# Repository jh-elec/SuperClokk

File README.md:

# SuperClokk

/*
*   8 x 8 LED Matrix Uhr
* 
* - BMP180  ( Luftdruck / Temperatur )
* - RX8564  ( RTC - Echtzeituhr )
* - DCF77   ( Uhrzeit  Funkempfänger )
*/

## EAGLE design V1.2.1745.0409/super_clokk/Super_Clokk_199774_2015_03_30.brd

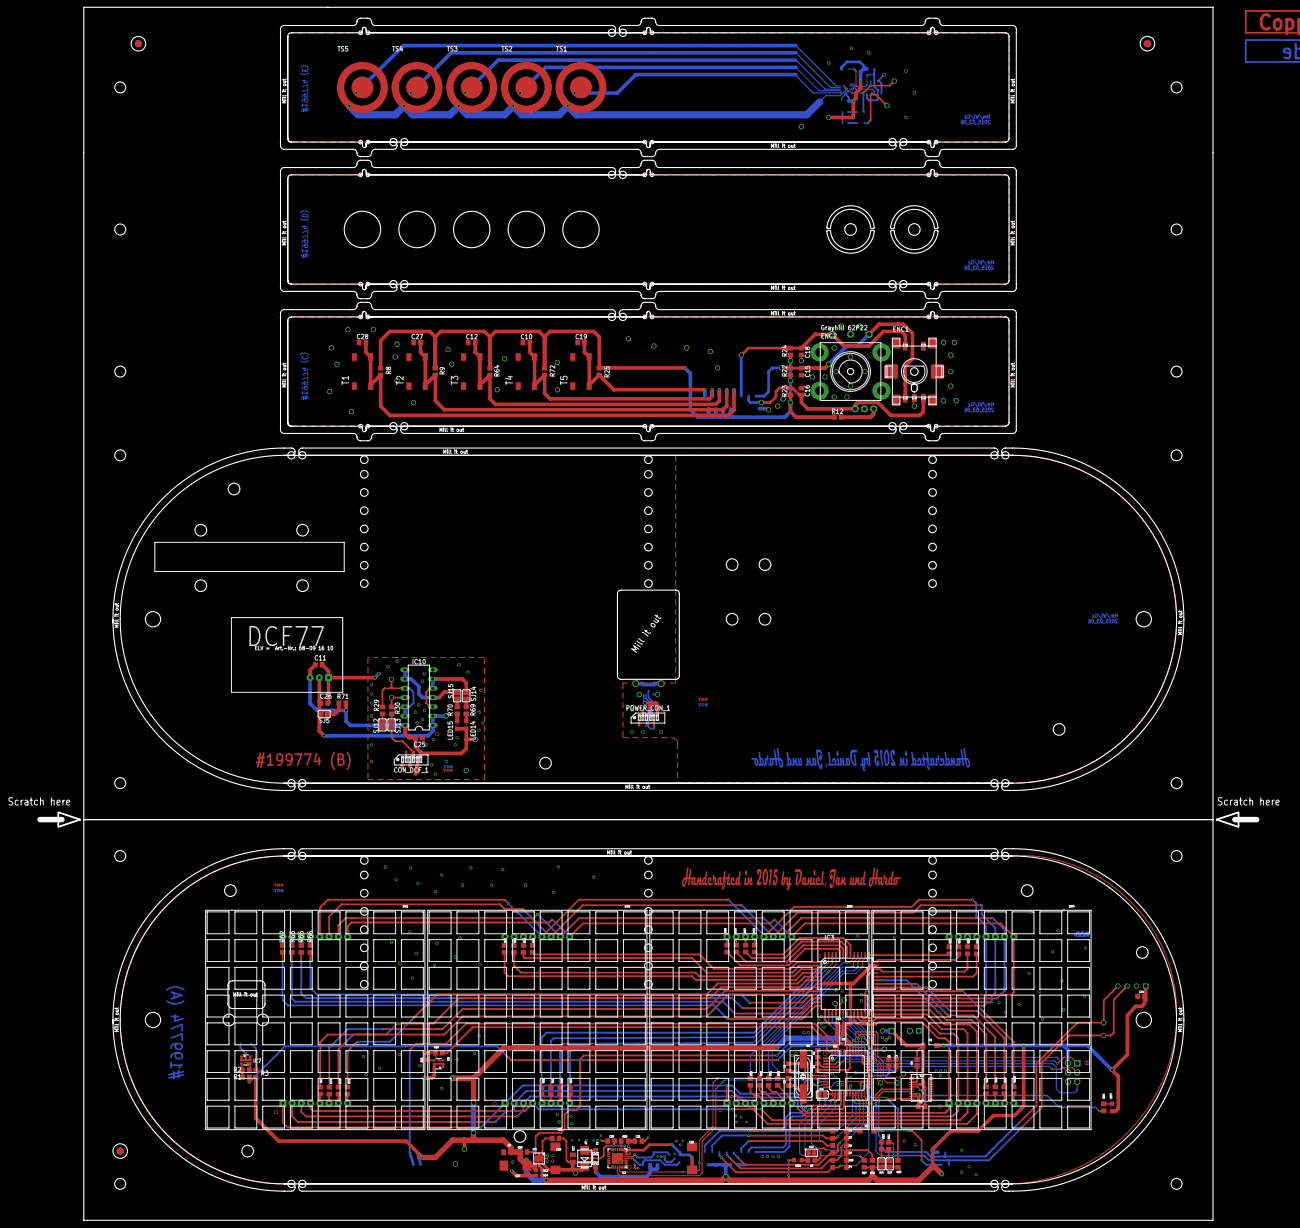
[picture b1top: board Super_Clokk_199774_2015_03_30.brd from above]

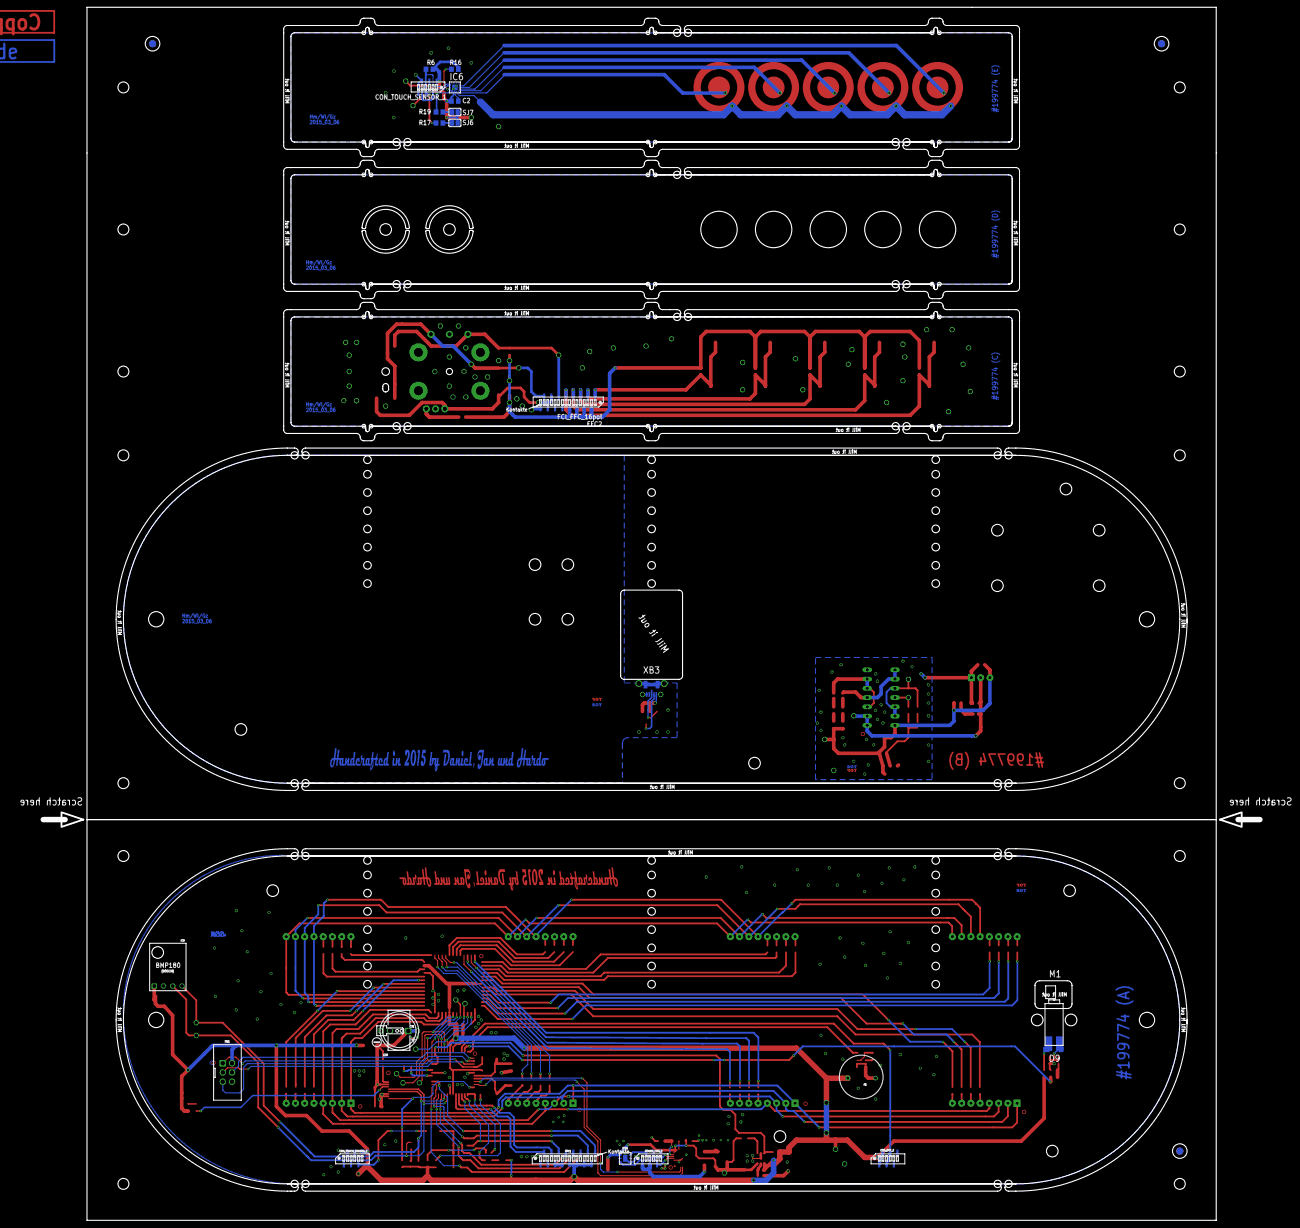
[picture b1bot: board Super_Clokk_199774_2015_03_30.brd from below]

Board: 2 copper layers, 334.0 x 333.0 mm, 211 parts (28 on the bottom side), 175 nets.

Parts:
A1: FUCW03THT; FUCW03
A3: ELV68-09-16-10; 18X23MM
C1, C2, C5, C6, C7, C9, C10, C11, C12, C14, C15, C16, C18, C19, C20, C21, C24, C25, C27, C28: 100n; C0805
C3, C4: 22p; C0805K
C8, C17: 1u; C0805K
C22, C23, C29: 100µ; SMC_D
C26: 10n; C0805
C30: PANASONIC_SD_SERIES_STEHEND
C31: PANASONIC_SD_SERIES_LIEGEND
CON_DCF_1, CON_DCF_2: MOLEX_52808_0671_NON_ZIF; MOLEX_52808-0671_NON_ZIF
CON_TOUCH_SENSOR_1, CON_TOUCH_SENSOR_2: MOLEX_52808_0671_NON_ZIF; MOLEX_52808-0671_NON_ZIF
D1, D2, D3, D4, D5, D6, D8, D9, D10: BAS116H-115; SOD123
D7: SS24R4; DO-214AA/SMB
DIS1, DIS2, DIS3, DIS4: TOYO-D24882; TOYO
ENC1: BOURNS_PEC11S
ENC2: Grayhill 62P22; 62P22
F2: MF-NSMF200; 1206L
FFC1, FFC2: FCI_FFC_16pol; MOLEX_52808_1671_NON_ZIF
IC1: CP2102SMD; QFN28
IC2: VSOJ20
IC3: HT1632-C; 52PIN_OFP
IC4: LD39050PUR; DFN6
IC5, IC7: PMN28-UN; SOT457
IC6: AT42QT2120-MMH; VQFN-20
IC8: MEGA32-A; TQFP44
IC9: BOSCH-BMP180; 10X13MM
IC10: 4093N; DIL14
IC11: TPD2E001DRSR; DRS
LED2, LED7, LED14, LED15: CHIPLED_0805
M1: VIBROMOTORTHT432A; LA4-432A
MAINFRAME: PLATINENKONTUR_310X220_FULLY_ROUNDED
POWER_CON_1, POWER_CON_2: FCI_FFC_6_pol; MOLEX_52808-0671_NON_ZIF
Q2: HC49-U / 16 MHz; HC49
R1, R4, R5, R10, R18, R29, R30, R69, R70: 1k; R0805
R2, R7, R8, R9, R11, R15, R20, R21, R25, R26, R27, R28, R64, R71, R72: 100k; R0805
R3: 47R; R0805
R6, R16, R17, R19, R22, R23, R24: 10k; R0805
R12: 100R; R0805
R13: 470k; R0603
R14: 150k; R0603
R52, R53: 4,7k; R0805
R62, R63, R65, R66, R67, R74, R75, R76, R77, R78, R79, R80, R81, R82, R83, R84, R85, R86, R87, R88, R89, R90, R91, R92, R93, R94, R95, R96, R97, R98, R99, R100: 22R; R0805
REF1, REF2, REF3: PASSER_2MM
SJ1, SJ2, SJ3, SJ4, SJ5, SJ6, SJ7, SJ12, SJ13, SJ14, SJ15: SJ
T1, T2, T3, T4, T5: OMRON-B3S-1002P; B3S-1002P
TP1, TP2, TP3, TP4, TP5, TP6, TP7, TP8, TP9, TP10, TP11, TP12, TP13, TP14, TP15, TP16, TP17, TP18, TP19, TP20: THT-1X2,54
TS1, TS2, TS3, TS4, TS5: TOUCH_SENSOR_14MM
U$1, U$6, U$8: BOT
U$2, U$9: HANDCRAFTED_WL_HM_GZ
U$3, U$4, U$5: TOP
U$7, U$24: WENN_GIRLSDAY_DANN_NUR_BEI_HESCH_LAYER_2
U$10, U$11, U$13: BESCHRIFTUNG_MECHANISCHE_TASTEN
U$12: WENN_GIRLSDAY_DANN_NUR_BEI_HESCH_LAYER_15
U$17, U$21, U$22, U$23: HESCH_LOGO_BIENE_LAYER_15
U$18, U$19, U$20: HESCH_LOGO_BIENE_LAYER_2
XB3: MICRODX4R005JJ2; MICRO_NEU
XW1: WSL

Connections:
+3V3: A1.+, C8.1, C9.1, C14.2, C23.+, C24.1, CON_DCF_2.1, CON_DCF_2.2, CON_TOUCH_SENSOR_2.6, D1.A, FFC1.9, FFC1.11, FFC1.13, FFC1.15, IC3.7, IC3.21, IC3.38, IC4.4, IC8.5, IC8.17, IC8.38, IC9.1, LED2.A, LED7.A, R3.1, R7.2, R13.1, R15.1, R20.2, R26.2, R27.2, SJ3.2, SJ4.2, TP8.TP, XW1.2
+3V3_TOUCH_SENSOR_MODUL: C2.1, CON_TOUCH_SENSOR_1.1, IC6.9, R6.2, R16.2, SJ6.2, SJ7.2, TP19.TP
ABORT_ALL_FUNCTIONS: C19.1, FFC2.1, R25.2, T5.1, T5.2
ABORT_ALL_FUNCTIONS_TO_CONNECTOR: D2.C, FFC1.16, IC8.25
AREF: C7.1, IC8.29
AVCC: C6.1, IC8.27
CHANGE_INT_TOUCH: CON_TOUCH_SENSOR_1.2, IC6.15, R6.1
CLKOUT: IC2.5, R18.1
COL_0: DIS1.1, DIS2.1, DIS3.1, DIS4.1, IC3.22
COL_1: DIS1.2, DIS2.2, DIS3.2, DIS4.2, IC3.23
COL_2: DIS1.3, DIS2.3, DIS3.3, DIS4.3, IC3.24
COL_3: DIS1.4, DIS2.4, DIS3.4, DIS4.4, IC3.26
COL_4: DIS1.12, DIS2.12, DIS3.12, DIS4.12, IC3.27
COL_5: DIS1.11, DIS2.11, DIS3.11, DIS4.11, IC3.28
COL_6: DIS1.10, DIS2.10, DIS3.10, DIS4.10, IC3.29
COL_7: DIS1.9, DIS2.9, DIS3.9, DIS4.9, IC3.30
CP2102_RESET: IC1.9, R28.2
CP2102_RXD: IC1.25, IC8.10
CP2102_TXD: IC1.26, IC8.9
D1_ROW0: DIS1.16, R62.1
D1_ROW1: DIS1.15, R63.1
D1_ROW2: DIS1.14, R65.1
D1_ROW3: DIS1.13, R66.1
D1_ROW4: DIS1.5, R67.1
D1_ROW5: DIS1.6, R74.1
D1_ROW6: DIS1.7, R75.1
D1_ROW7: DIS1.8, R76.1
D2_ROW0: DIS2.16, R77.1
D2_ROW1: DIS2.15, R78.1
D2_ROW2: DIS2.14, R79.1
D2_ROW3: DIS2.13, R80.1
D2_ROW4: DIS2.5, R81.1
D2_ROW5: DIS2.6, R82.1
D2_ROW6: DIS2.7, R83.1
D2_ROW7: DIS2.8, R84.1
D3_ROW0: DIS3.16, R85.1
D3_ROW1: DIS3.15, R86.1
D3_ROW2: DIS3.14, R87.1
D3_ROW3: DIS3.13, R88.1
D3_ROW4: DIS3.5, R89.1
D3_ROW5: DIS3.6, R90.1
D3_ROW6: DIS3.7, R91.1
D3_ROW7: DIS3.8, R92.1
D4_ROW0: DIS4.16, R93.1
D4_ROW1: DIS4.15, R94.1
D4_ROW2: DIS4.14, R95.1
D4_ROW3: DIS4.13, R96.1
D4_ROW4: DIS4.5, R97.1
D4_ROW5: DIS4.6, R98.1
D4_ROW6: DIS4.7, R99.1
D4_ROW7: DIS4.8, R100.1
D+: IC1.4, IC11.3, POWER_CON_2.5
D-: IC1.5, IC11.6, POWER_CON_2.2
DCF77_MODUL_OUT_INVERTED: A3.2, C26.1, IC10.1, IC10.2, SJ5.2, TP15.TP
DCF77_buffFERED_INVERTED_FROM_DCF77_MODUL: CON_DCF_2.3, CON_DCF_2.4, IC8.42
DCF77_buffF_INVERTED: IC10.4, IC10.8, IC10.9, SJ15.2
DCF77_buffF_NON_INVERTED: IC10.10, IC10.12, IC10.13, R29.2, TP17.TP
DCF77_buffF_OUT_SWITCHABLE: CON_DCF_1.3, CON_DCF_1.4, SJ12.1, SJ13.1
EINGABE?: D2.A, D3.A, D4.A, D5.A, D6.A, D8.A, D10.A, R26.1, SJ2.2
ENCODER_A: C15.1, ENC1.A, ENC2.4, FFC2.15, R22.1
ENCODER_A_TO_CONNECTOR: FFC1.2, IC8.16
ENCODER_B: C16.1, ENC1.B, ENC2.3, FFC2.13, R23.1
ENCODER_B_TO_CONNECTOR: FFC1.4, IC8.15
GND: C1.2, C3.2, C4.2, C5.2, C6.2, C7.2, C8.2, C9.2, C14.1, C17.2, C20.2, C21.2, C22.-, C23.-, C24.2, C29.-, C30.-, C31.MINUS, CON_DCF_2.5, CON_DCF_2.6, CON_TOUCH_SENSOR_2.1, CON_TOUCH_SENSOR_2.2, FFC1.1, FFC1.3, FFC1.5, FFC1.7, IC1.3, IC1.THERMAL, IC2.8, IC2.9, IC3.14, IC3.25, IC3.36, IC4.2, IC4.EXP, IC5.4, IC7.4, IC8.6, IC8.18, IC8.28, IC8.39, IC9.2, IC11.4, IC11.THERMAL, POWER_CON_2.4, POWER_CON_2.6, R2.2, R11.2, R14.2, TP9.TP, XW1.6
GND_DCF77: A3.1, C11.2, C25.2, C26.2, CON_DCF_1.1, CON_DCF_1.2, IC10.7, TP14.TP
GND_SWITCHBOARD: C10.2, C12.2, C15.2, C16.2, C18.2, C19.2, C27.2, C28.2, ENC1.C, ENC1.E, ENC1.SHIELD_1, ENC1.SHIELD_2, ENC1.SHIELD_3, ENC1.SHIELD_4, ENC1.SHIELD_5, ENC1.SHIELD_6, ENC2.2, ENC2.5, FFC2.10, FFC2.12, FFC2.14, FFC2.16, T1.3, T1.4, T2.3, T2.4, T3.3, T3.4, T4.3, T4.4, T5.3, T5.4
GND_TOUCH: C2.2, CON_TOUCH_SENSOR_1.5, CON_TOUCH_SENSOR_1.6, IC6.8, IC6.10, IC6.EXP., TP20.TP
GND_USB_RüCKWAND: POWER_CON_1.1, POWER_CON_1.3, XB3.5, XB3.6, XB3.7, XB3.8, XB3.9, XB3.10, XB3.11
HEARTBEAT: IC8.13, R5.1
HT1632_CS: IC3.19, IC8.32, TP1.TP
HT1632_DATA: IC3.16, IC8.35, TP4.TP
HT1632_OSC: IC3.15, IC8.37, TP11.TP
HT1632_RD: IC3.18, IC8.33, TP2.TP
HT1632_SYNC: IC3.20, IC8.36, TP16.TP
HT1632_WR: IC3.17, IC8.34, TP3.TP
INTERRUPT_TOUCH_SENSOR: CON_TOUCH_SENSOR_2.5, D8.C
LD39050-PG: IC4.3, IC8.31, R15.2
MISO: IC8.2, XW1.1
MOSI: IC8.1, XW1.4
unnamed: A1.-, IC5.1, IC5.2, IC5.5, IC5.6
unnamed: R52.2, SJ3.1
unnamed: R53.2, SJ4.1
unnamed: R71.2, SJ5.1
unnamed: IC7.3, R1.1, R2.1
unnamed: C21.1, IC1.6, R28.1
unnamed: D7.A, F2.2
unnamed: D9.A, IC7.1, IC7.2, IC7.5, IC7.6, M1.2
unnamed: D9.C, M1.1, R3.2
unnamed: IC3.13, R62.2
unnamed: IC4.1, R21.2
unnamed: IC2.3, R4.1
unnamed: IC3.12, R63.2
unnamed: IC4.5, R13.2, R14.1
unnamed: IC5.3, R10.1, R11.1
unnamed: LED2.C, R5.2
unnamed: IC6.7, TS1.GUARD, TS2.GUARD, TS3.GUARD, TS4.GUARD, TS5.GUARD
unnamed: IC3.11, R65.2
unnamed: IC10.3, IC10.5, IC10.6, SJ14.2
unnamed: IC3.10, R66.2
unnamed: IC3.9, R67.2
unnamed: ENC2.1, R12.1
unnamed: IC6.12, R16.1
unnamed: IC8.12, SJ1.1, SJ2.1
unnamed: LED7.C, R18.2
unnamed: IC6.6, TS1.TOUCH
unnamed: IC6.5, TS2.TOUCH
unnamed: IC6.4, TS3.TOUCH
unnamed: IC6.3, TS4.TOUCH
unnamed: IC6.2, TS5.TOUCH
unnamed: R17.1, SJ6.1
unnamed: R19.1, SJ7.1
unnamed: IC10.11, R30.2, TP7.TP
unnamed: R29.1, SJ12.2
unnamed: R30.1, SJ13.2
unnamed: R69.1, SJ14.1
unnamed: R70.1, SJ15.1
unnamed: R27.1, SJ1.2
unnamed: IC3.8, R74.2
unnamed: LED14.C, R69.2
unnamed: LED15.C, R70.2
unnamed: IC3.6, R75.2
unnamed: IC3.5, R76.2
unnamed: IC3.4, R77.2
unnamed: IC3.3, R78.2
unnamed: IC3.2, R79.2
unnamed: IC3.1, R80.2
unnamed: IC3.52, R81.2
unnamed: IC3.51, R82.2
unnamed: IC3.50, R83.2
unnamed: IC3.49, R84.2
unnamed: IC3.48, R85.2
unnamed: IC3.47, R86.2
unnamed: IC3.46, R87.2
unnamed: IC3.45, R88.2
unnamed: IC3.44, R89.2
unnamed: IC3.43, R90.2
unnamed: IC3.42, R91.2
unnamed: IC3.41, R92.2
unnamed: IC3.40, R93.2
unnamed: IC3.39, R94.2
unnamed: IC3.37, R95.2
unnamed: IC3.35, R96.2
unnamed: IC3.34, R97.2
unnamed: IC3.33, R98.2
unnamed: IC3.32, R99.2
unnamed: IC3.31, R100.2
POWER_FROM_USB_RüCKWAND: F2.1, POWER_CON_2.1, POWER_CON_2.3
PUSHBUTTON: C18.1, ENC1.D, ENC2.6, FFC2.11, R24.1
PUSHBUTTON_TO_CONNECTOR: D6.C, FFC1.6, IC8.14
PWM_DOWN: C27.1, FFC2.7, R9.2, T2.1, T2.2
PWM_DOWN_TO_CONNECTOR: D10.C, FFC1.10, IC8.22
PWM_UP: C28.1, FFC2.9, R8.2, T1.1, T1.2
PWM_UP_TO_CONNECTOR: D5.C, FFC1.8, IC8.21
RESET_ATMEL: C5.1, IC8.4, R7.1, XW1.5
RTC8564_INT: IC2.10, IC8.11, R20.1
SCK: IC8.3, XW1.3
SCL: CON_TOUCH_SENSOR_2.3, IC2.6, IC8.19, IC9.3, R52.1, TP6.TP
SCL_TOUCH_SENSOR: CON_TOUCH_SENSOR_1.4, IC6.14, R17.2, TP12.TP
SDA: CON_TOUCH_SENSOR_2.4, IC2.7, IC8.20, IC9.4, R53.1, TP5.TP
SDA_TOUCH_SENSOR: CON_TOUCH_SENSOR_1.3, IC6.11, R19.2, TP13.TP
SET+: C12.1, FFC2.5, R64.2, T3.1, T3.2
SET+_TO_CONNECTOR: D4.C, FFC1.12, IC8.23
SET-: C10.1, FFC2.3, R72.2, T4.1, T4.2
SET-_TO_CONNECTOR: D3.C, FFC1.14, IC8.24
SOUND: IC8.44, R10.2
SUPPLY_3V3_BEDIENMODUL: FFC2.2, FFC2.4, FFC2.6, FFC2.8, R8.1, R9.1, R12.2, R22.2, R23.2, R24.2, R25.1, R64.1, R72.1
SUPPLY_3V3_DCF77: A3.3, C11.1, C25.1, CON_DCF_1.5, CON_DCF_1.6, IC10.14, LED14.A, LED15.A, R71.1, TP18.TP
SUPPLY_RTC: C1.1, C30.+, C31.PLUS, D1.C, IC2.4, R4.2
USB_D+: POWER_CON_1.2, XB3.3
USB_D-: POWER_CON_1.5, XB3.2
VBUS_USB_RüCKWAND: POWER_CON_1.4, POWER_CON_1.6, XB3.1
VCC: C17.1, C20.1, C22.+, C29.+, D7.C, IC1.7, IC1.8, IC4.6, IC11.1, R21.1, TP10.TP
VIBRO_MOTOR: IC8.43, R1.2
XTAL_1: C3.1, IC8.8, Q2.1
XTAL_2: C4.1, IC8.7, Q2.2

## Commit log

2018-09-05 Wenn das Datum gescrollt wird, war bei der "KW" ( Kalenderwoche ) ein paar Leerzeichen zu wenig.. Diese wurden ergänzt
2018-09-10 Umrechnung der Übergabeparameter für die Funktion -> scrollDate(..) geändert.
2018-09-11 - Bug bei beim ablegen der EEProm Daten nach dem Sync. behoben. - Bug beim ändern der Helligkeit behoben.
2018-09-13 Treiber für die Echtzeituhr angepasst
2024-12-15 mini edit
